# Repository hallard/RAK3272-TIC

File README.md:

# RAK3272 TIC (Teleinfo) LoRaWAN Shield

This shield is used to get French energy meter called Teleinfo data with WisDuo LoRaWAN RAK3272 SIP Breakout board:

&nbsp;

# Detailed Description

**V1.0**

- On Board 3.3V regulator used when powering thru batteries (Vin > 3.6V)
- Low Power Mode option driving some GPIO to disable TIC
- Led to indicated TIC reception signal
- User Red and Green Led 
- User button (pull down)
- On board I2C Pullups (4K7)
- Footprint for Battery connector 
- QWICC / Stemma standard connector

:warning: Despite the fact that RAK3272-SIP Breakout announced as xBee format, this is far from the case because:

- xBee as 16 pins on the header this one 18 pins
- xBee pinout is totally different (power and other)
- least but not least, headers spacing of external raws of RAK3272 are different than xBee.

So in V1.0 version of my shield you will need to bend headers of RAK3272 and shield so you can plug it, that's a shame.

Anyway, if you're designing shield for RAK3272 don't take xBee spacing format for external headers, it won't fit 

# Pinout

Look at the schematics for more informations, easy to understand. Wiring on the RAK3272 Teleinfo shield is as follow:

| Pin Function | RAK3272   | STM32WL |
|  :---        |  :---:    |  :---:  | 
| TIC Rx       | UART1_RX  |   PB7   |
| TIC Enable   | SPI1_CLK  |   PA5   | 
| Led TIC      |   PA8     |   PA8   | 
| Led Red      | SPI1_MISO |   PA6   | 
| Led Green    | SPI1_MOSI |   PA7   | 
| Button       | SPI1_NSS  |   PA4   | 
| I2C SDA      | I2C2_SDA  |  PA11   |
| I2C SDL      | I2C2_SCL  |  PA12   |

:warning: Button is `boot0` button, to avoid adding one more button for user, I wired Boot0 to `PA4` to we can read button state, but since it's `boot0` it has pulldown resistor and it is active High.

To enable reading Téléinfo you need:

- Drive High ping `PA5` (mandatory)
- Drive High ping `PA8` (to eable TIC Led to blink on data reception on Serial)
- Read Teleinfo on `UART1_RX` (`PB7`)

# Schematics

# Boards

## Assembled (V1.0)

&nbsp;&nbsp;

## Shield Plugged on RAK3272 SIP Breakout

&nbsp;

# Firmware 

You can write your own and use with [LibTeleinfo](https://github.com/hallard/LibTeleinfo) library I wrote if you want to get rid of driving teleinfo stuff (chekout some [examples](ttps://github.com/hallard/LibTeleinfo/tree/master/examples)).

To Be Completed

## I2C 

You can add fancy I2C display or even I2C sensors, there is a Stemma QWIIC connector on board. Since I2C VCC is conencted to 3.3V, your I2C should works in 3.3V or 5V or 5V ones (They all have level shifter since majorty of sensors works at 3.3V)

# Support and discussion

If you have any issue or just want to discuss on this project, please use community [forum](https://community.ch2i.eu/category/19/wemos-teleinfo)

# License

This work is licensed under a [Creative Commons Attribution-NonCommercial 4.0 International License](http://creativecommons.org/licenses/by-nc/4.0/)    
If you want to do commercial stuff with this project, please contact [CH2i company](https://ch2i.eu/en#support) so we can organize an simple agreement.

# Lazy building your own? 

You can order this shield fully assembled with some extra on tindie (soon, may be)

# Misc

See news and other projects on my [blog][2] 
 
[2]: https://hallard.me

[20]: https://store.rakwireless.com/products/wisduo-breakout-board-rak3272-sip
[21]: https://docs.rakwireless.com/Product-Categories/WisDuo/RAK3272-SiP-Breakout-Board/Datasheet
[22]: https://www.smart-prototyping.com/Mini-D1-PRO-Development-Board-ESP8266-4M-16M
[23]: https://www.az-delivery.de/fr/products/esp32-d1-mini
[24]: https://www.tindie.com/products/25467/

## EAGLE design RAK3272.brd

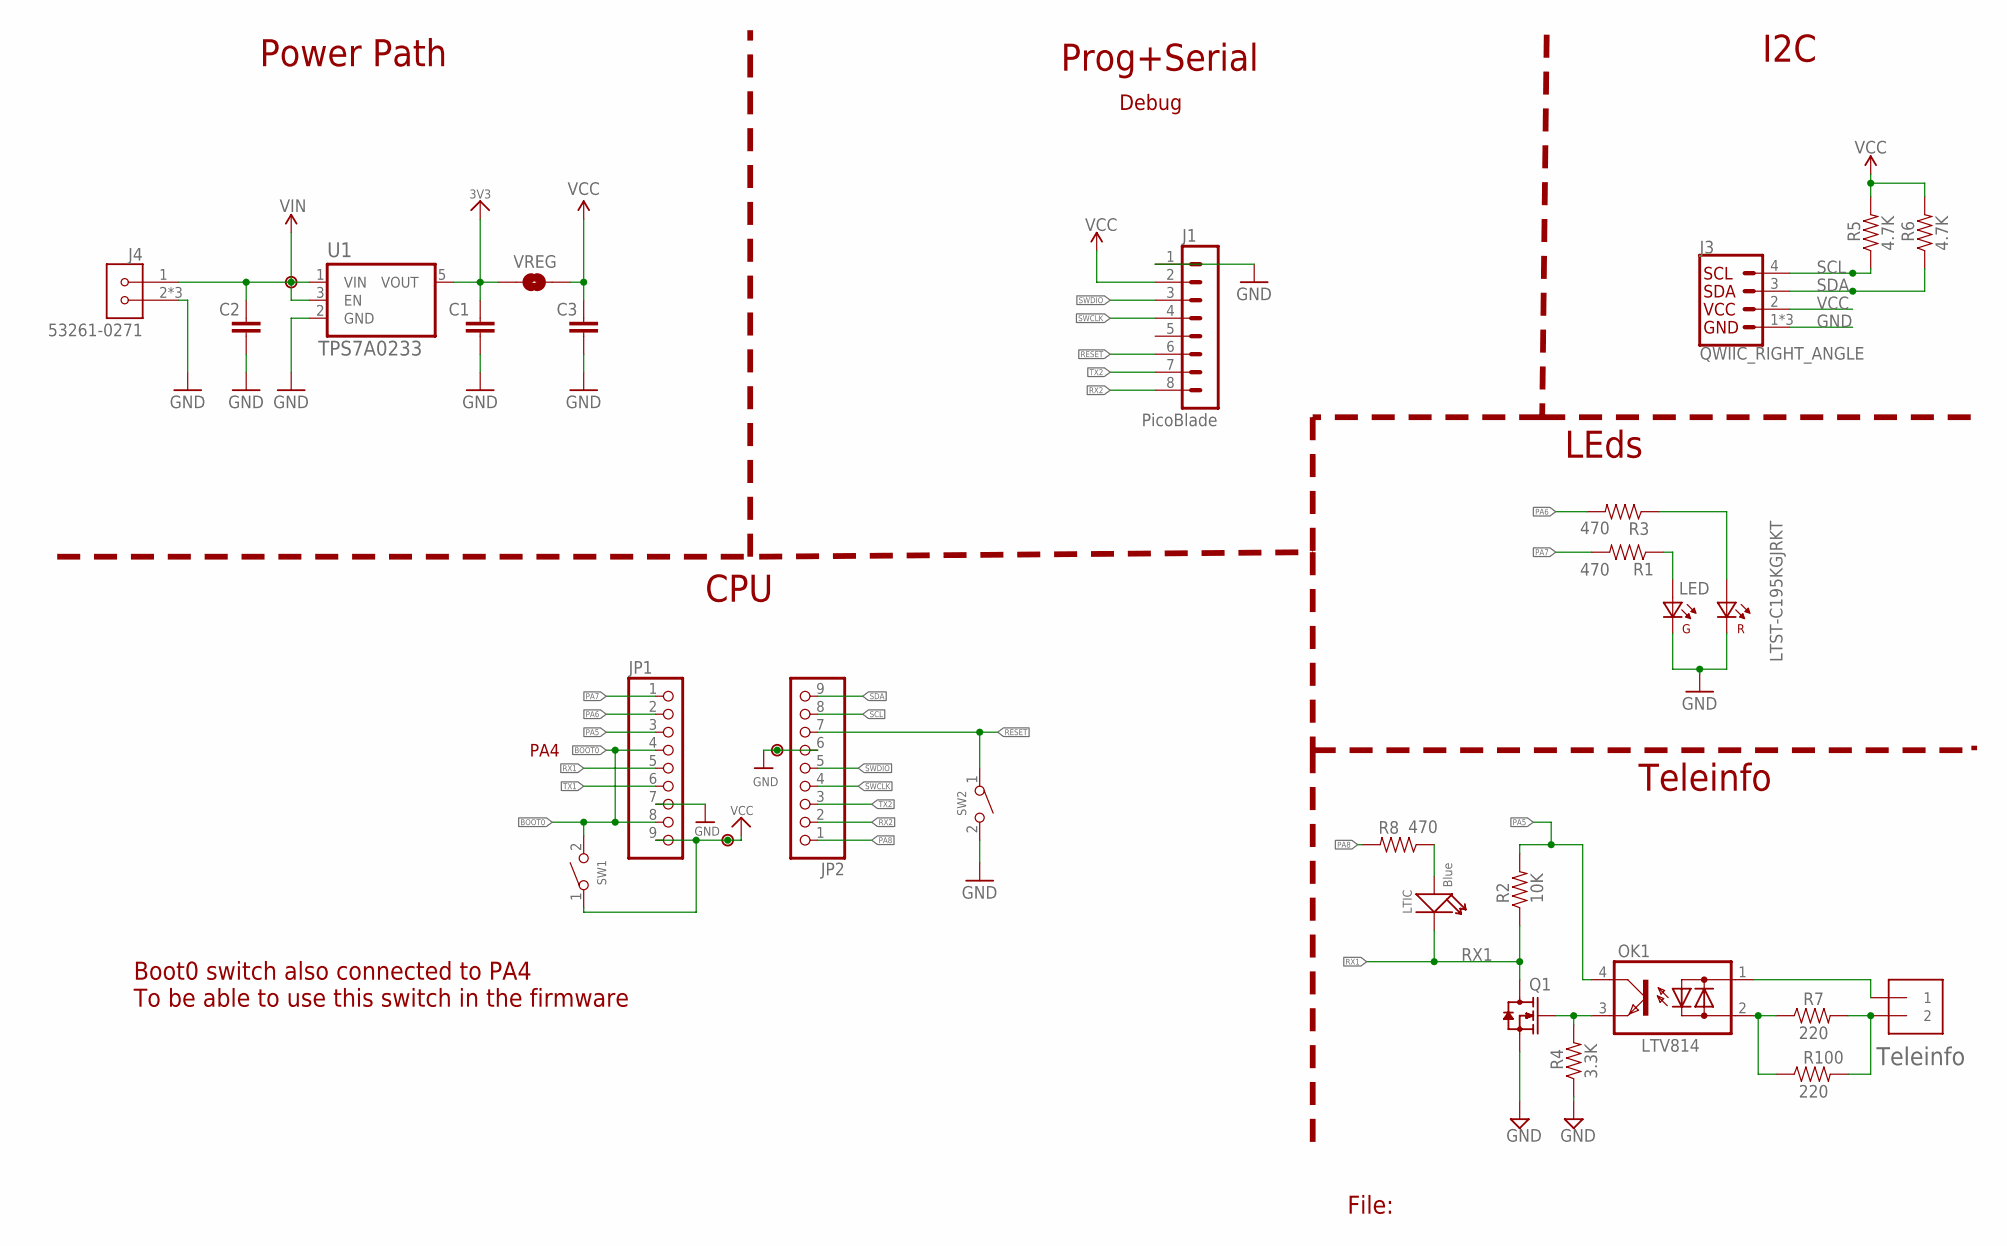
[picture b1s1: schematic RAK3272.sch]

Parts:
C1, C2, C3: 1.0uF; 0402-CAP-OK
J1: PicoBlade; 53047-0810
J2: 1X2-3.5MM
J3: QWIIC_RIGHT_ANGLE; JST04_1MM_HORI
J4: 53261-0271; MOLEX_53261-0271
JP1, JP2: PINHD-1X9; 1X09-BIG
LED: LTST-C195KGJRKT; LTST-BILED-15X16
LTIC: Blue; LED-0402
OK1: LTV814; DIL4-SMD
P1, P2, P3: PADNORMAL; PAD
Q1: CJ2302; SOT-323-3
R1, R3, R8: 470; 0402-RES
R2: 10K; 0402-RES
R4: 3.3K; 0402-RES
R5, R6: 4.7K; 0402-RES
R7: 220; 0402-RES
R100: 220; 1206
SW1, SW2: B3U-1000P-2P-SMD; C498294
U1: TPS7A0233; SOT95P280X145-5N
VREG: JUMPER-SMT_2_NO_NO-SILK; SMT-JUMPER_2_NO_NO-SILK

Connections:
3V3: C1.1, U1.5 (VOUT), VREG.2
BOOT0: JP1.4, JP1.8, SW1.2
GND: C1.2, C2.2, C3.2, J1.1, J3.1, J3.NC1 (1), J3.NC2 (1), J4.2, J4.P1 (2), J4.P2 (2), JP1.7, JP2.6, LED.P$3 (K1), LED.P$4 (K2), P2.1, Q1.2 (S), R4.1, SW2.2, U1.2 (GND)
unnamed: LED.P$2 (A2), R3.1
unnamed: LED.P$1 (A1), R1.1
unnamed: OK1.2 (AC2), R7.1, R100.1
unnamed: J2.1, OK1.1 (AC1)
unnamed: J2.2, R7.2, R100.2
unnamed: OK1.3 (E), Q1.1 (G), R4.2
unnamed: LTIC.+, R8.1
PA5: JP1.3, OK1.4 (C), R2.2
PA6: JP1.2, R3.2
PA7: JP1.1, R1.2
PA8: JP2.1, R8.2
RESET: J1.6, JP2.7, SW2.1
RX1: JP1.5, LTIC.-, Q1.3 (D), R2.1
RX2: J1.8, JP2.2
SCL: J3.4, JP2.8, R5.1
SDA: J3.3, JP2.9, R6.1
SWCLK: J1.4, JP2.4
SWDIO: J1.3, JP2.5
TX1: JP1.6
TX2: J1.7, JP2.3
VCC: C3.1, J1.2, J3.2, JP1.9, P3.1, R5.2, R6.2, SW1.1, VREG.1
VIN: C2.1, J4.1, P1.1, U1.1 (VIN), U1.3 (EN)

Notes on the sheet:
File:
Teleinfo
I2C
LEds
Power Path
CPU
Prog+Serial
Debug
Boot0 switch also connected to PA4 To be able to use this switch in the firmware
PA4

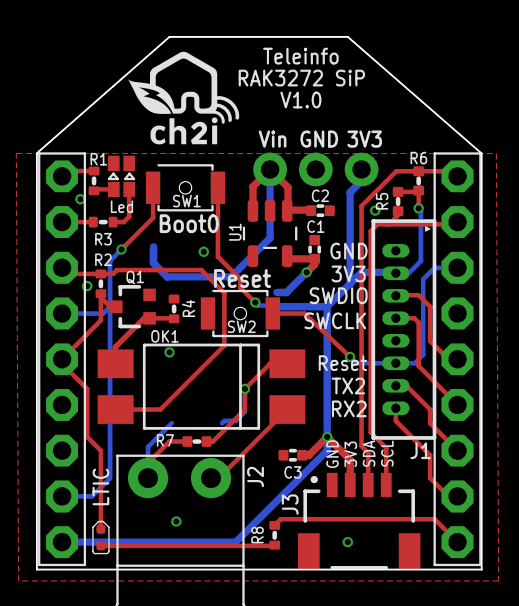
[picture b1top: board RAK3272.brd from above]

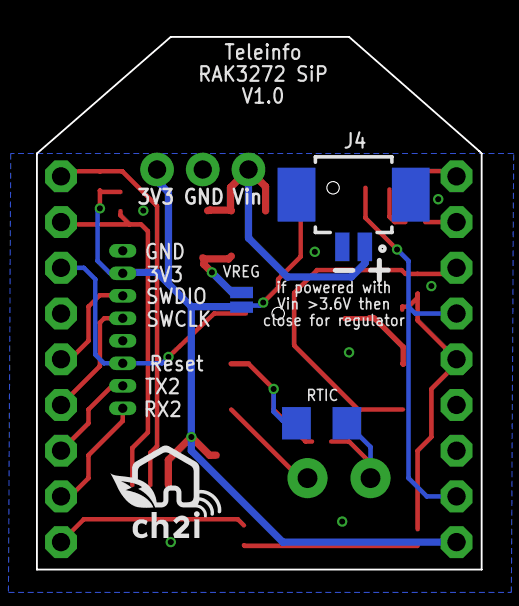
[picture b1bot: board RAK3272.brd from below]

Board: 2 copper layers, 24.7 x 29.6 mm, 31 parts (4 on the bottom side), 24 nets.

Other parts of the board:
$$U$1: LOGO_C2I_015
U$100: LOGO_C2I_015

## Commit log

2022-08-30 fixed pictures link
2022-08-30 Added button pin

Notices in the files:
parts and their libraries:
con-molex-picoblade: Copyright (C) 2010, Bob Starr
SparkFun-Jumpers: Licensing: Creative Commons ShareAlike 4.0 International - https://creativecommons.org/licenses/by-sa/4.0
